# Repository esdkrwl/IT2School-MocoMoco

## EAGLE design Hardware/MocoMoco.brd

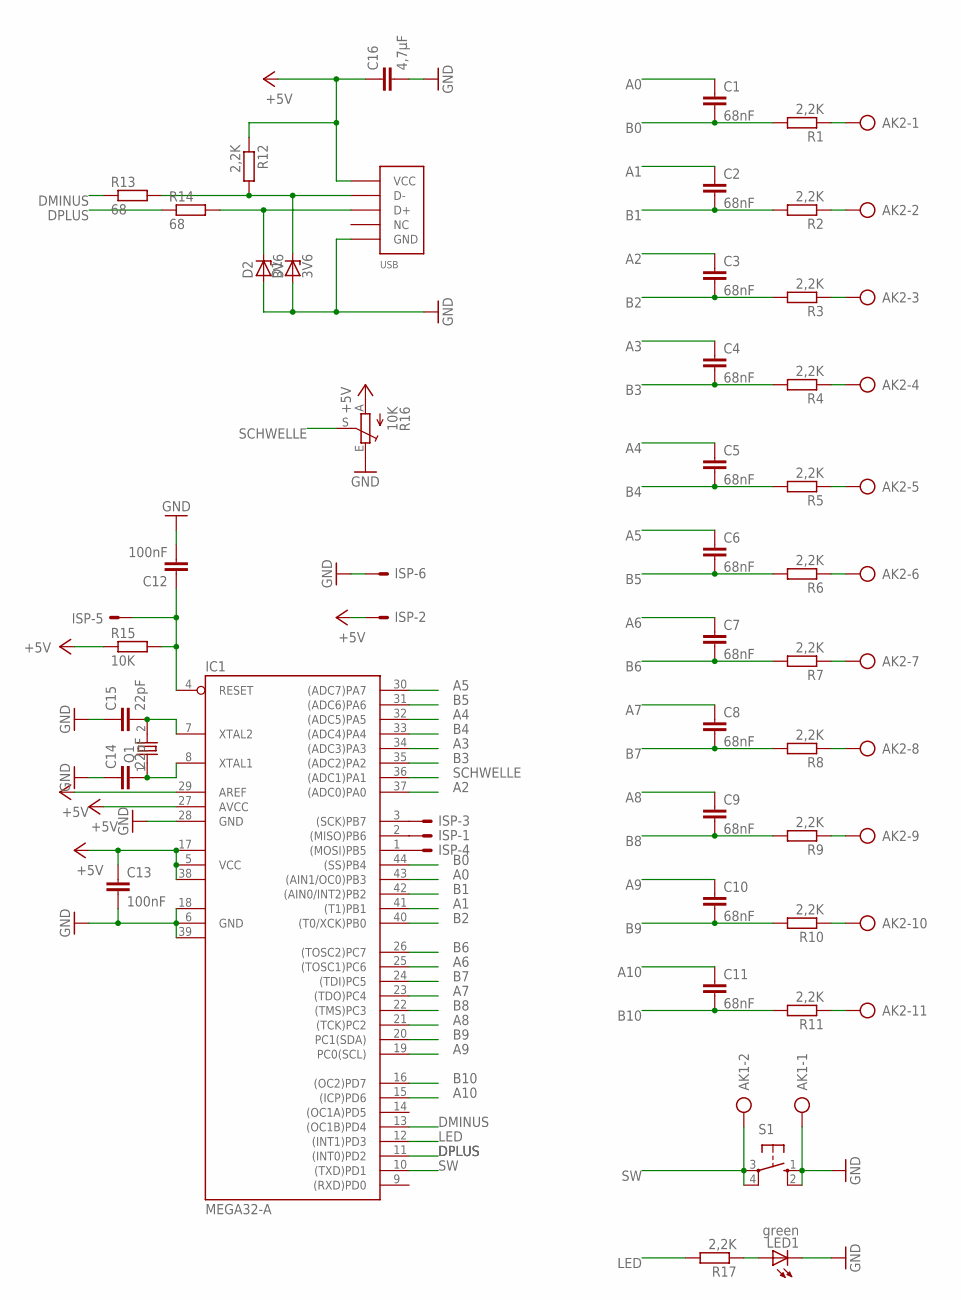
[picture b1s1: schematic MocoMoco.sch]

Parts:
AK1: AK2; AK/2
AK2: AK11; AK/11
C1, C2, C3, C4, C5, C6, C7, C8, C9, C10, C11: 68nF; C0805K
C12, C13: 100nF; C0805K
C14, C15: 22pF; C0805K
C16: 4,7µF; C3216
D1, D2: 3V6; TO236
IC1: MEGA32-A; TQFP44
ISP: ML6E; ML6
LED1: green; CHIP-LED0603
Q1: HC-49/US; HC49UP
R1, R2, R3, R4, R5, R6, R7, R8, R9, R10, R11, R12, R17: 2,2K; R0603
R13, R14: 68; R0603
R15: 10K; R0603
R16: 10K; LI10
S1: 10-XX; B3F-10XX
USB: MICRO_USB; MICRO_USB_A01SB141B1-292

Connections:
+5V: C13.1, C16.1, IC1.5 (VCC), IC1.17 (VCC1), IC1.27 (AVCC), IC1.29 (AREF), IC1.38 (VCC2), ISP.2, R12.1, R15.1, R16.A, USB.P$1 (VCC)
A0: C1.1, IC1.43 ((AIN1/OC0)PB3)
A1: C2.1, IC1.41 ((T1)PB1)
A2: C3.1, IC1.37 ((ADC0)PA0)
A3: C4.1, IC1.34 ((ADC3)PA3)
A4: C5.1, IC1.32 ((ADC5)PA5)
A5: C6.1, IC1.30 ((ADC7)PA7)
A6: C7.1, IC1.25 ((TOSC1)PC6)
A7: C8.1, IC1.23 ((TDO)PC4)
A8: C9.1, IC1.21 ((TCK)PC2)
A9: C10.1, IC1.19 (PC0(SCL))
A10: C11.1, IC1.15 ((ICP)PD6)
B0: C1.2, IC1.44 ((SS)PB4), R1.2
B1: C2.2, IC1.42 ((AIN0/INT2)PB2), R2.2
B2: C3.2, IC1.40 ((T0/XCK)PB0), R3.2
B3: C4.2, IC1.35 ((ADC2)PA2), R4.2
B4: C5.2, IC1.33 ((ADC4)PA4), R5.2
B5: C6.2, IC1.31 ((ADC6)PA6), R6.2
B6: C7.2, IC1.26 ((TOSC2)PC7), R7.2
B7: C8.2, IC1.24 ((TDI)PC5), R8.2
B8: C9.2, IC1.22 ((TMS)PC3), R9.2
B9: C10.2, IC1.20 (PC1(SDA)), R10.2
B10: C11.2, IC1.16 ((OC2)PD7), R11.2
DMINUS: IC1.13 ((OC1B)PD4), R13.1
DPLUS: IC1.11 ((INT0)PD2), R14.1
GND: AK1.1, C12.2, C13.2, C14.1, C15.1, C16.2, D1.A, D2.A, IC1.6 (GND), IC1.18 (GND1), IC1.28 (GND), IC1.39 (GND2), ISP.6, LED1.C, R16.E, S1.1 (S), S1.2 (S1), USB.P$5 (GND)
LED: IC1.12 ((INT1)PD3), R17.2
unnamed: AK2.1, R1.1
unnamed: AK2.2, R2.1
unnamed: C15.2, IC1.7 (XTAL2), Q1.2
unnamed: AK2.4, R4.1
unnamed: D1.C, R12.2, R13.2, USB.P$2 (D-)
unnamed: AK2.5, R5.1
unnamed: AK2.6, R6.1
unnamed: D2.C, R14.2, USB.P$3 (D+)
unnamed: AK2.7, R7.1
unnamed: IC1.1 ((MOSI)PB5), ISP.4
unnamed: IC1.3 ((SCK)PB7), ISP.3
unnamed: AK2.8, R8.1
unnamed: C12.1, IC1.4 (RESET), ISP.5, R15.2
unnamed: IC1.2 ((MISO)PB6), ISP.1
unnamed: AK2.9, R9.1
unnamed: AK2.10, R10.1
unnamed: AK2.11, R11.1
unnamed: AK2.3, R3.1
unnamed: C14.2, IC1.8 (XTAL1), Q1.1
unnamed: LED1.A, R17.1
SCHWELLE: IC1.36 ((ADC1)PA1), R16.S
SW: AK1.2, IC1.10 ((TXD)PD1), S1.3, S1.4 (P1)

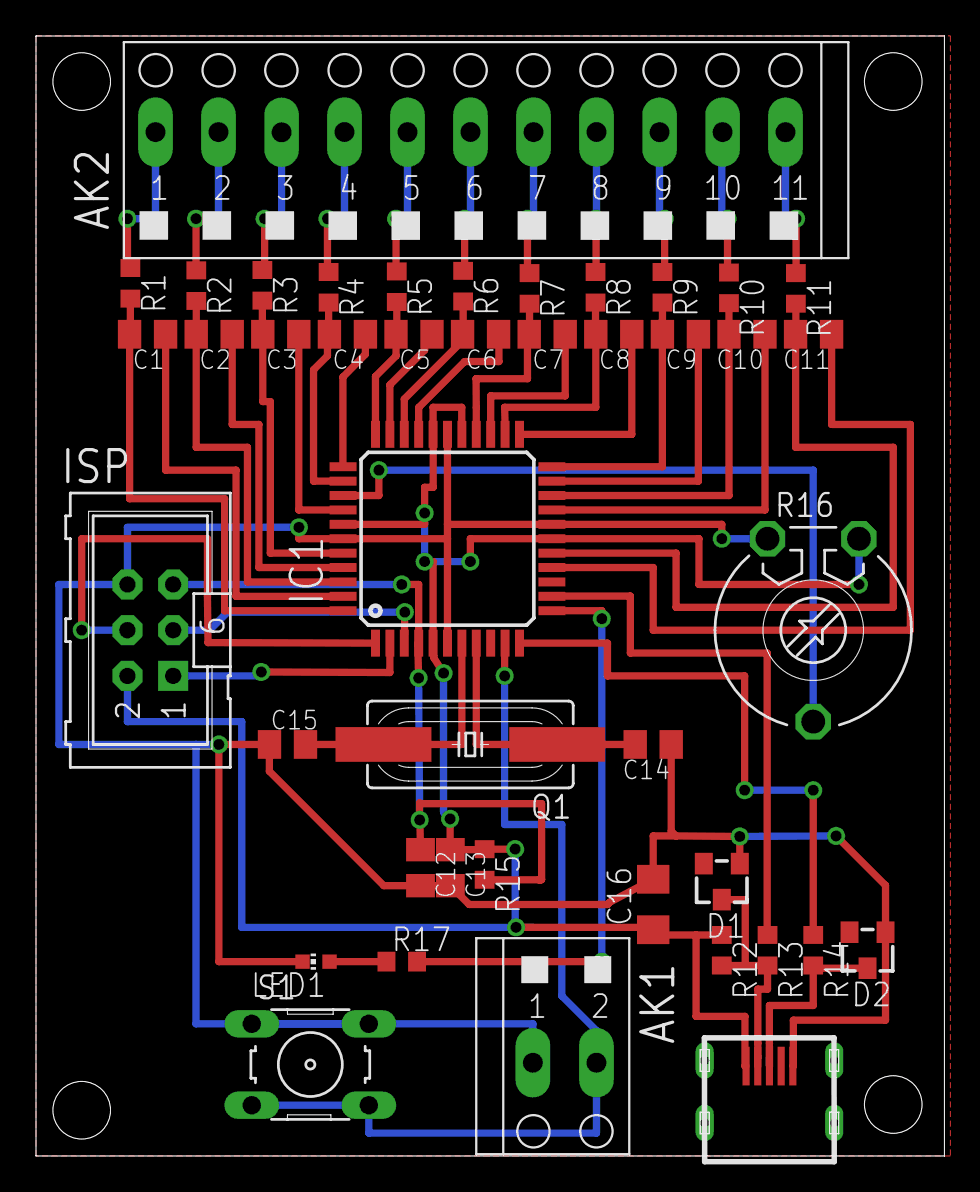
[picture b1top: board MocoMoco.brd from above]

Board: 2 copper layers, 50.5 x 62.2 mm, 43 parts (0 on the bottom side), 49 nets.

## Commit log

2022-11-03 init

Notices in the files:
Hardware/MocoMoco.brd:
copyright Tobias Stuckenberg
